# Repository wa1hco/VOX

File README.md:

# VOX — Voice Operated Switch for Ham Radio

A small-board VOX circuit using adaptive echo cancellation (AEC) and voice activity detection (VAD) to reliably key PTT from microphone audio while ignoring receive audio and background noise.

## Acronyms

- **AEC**: Adaptive Echo Cancellation
- **VAD**: Voice Activity Detection

## Features

- **AEC** — removes receive audio leaking into the microphone (anti-VOX), using SpeexDSP
- **VAD** — detects operator voice, ignores room noise, using SpeexDSP
- **Single control** — PTT hang time (ms); no level adjustments needed
- **3 LED status outputs**
	- `MIC LED`: microphone port activity/level present
	- `RX LED`: receive-audio port activity/level present
	- `VAD LED`: speech probability indicates likely operator voice
	- `AEC LED`: receive-audio leakage is being reduced by echo cancellation
	- `PTT LED`: transmit keying output is active
- **Linux simulation** — runs on a Linux PC for development and testing
- **MCU portable** — core library has no platform dependencies

## Building (Linux)

### Prerequisites

```sh
sudo apt install cmake libasound2-dev libspeexdsp-dev
```

For the Qt GUI on Linux:

```sh
sudo apt install qt6-base-dev
```

### Build

```sh
mkdir build && cd build
cmake ..
make
```

### Run

```sh
./vox_linux -h 500
```

Qt GUI run:

```sh
./vox_qt
```

The Qt test GUI shows:
- microphone level bargraph
- VAD output score (0-100)
- speaker monitor level bargraph
- AEC score (estimated reduction %)
- PTT ON/OFF indicator
- MCU-style LED panel: MIC, RX, VAD, AEC, PTT
- live tuning sliders for:
	- PTT hang time
	- MIC activity threshold
	- RX activity threshold
	- VAD probability threshold
	- AEC reduction threshold

By default on Linux desktop systems, `vox_linux` auto-selects:
- the default microphone source for `MIC`
- the monitor source of the default speaker sink for `RX`

Options:
- `--list-devices` — print available capture devices and exit
- `-m <device>` — microphone capture device (default `auto`)
- `-r <device>` — receive-reference capture device (default `auto`)
- `-h <ms>` — PTT hang time in milliseconds (default `500`)
- `-M <level>` — MIC LED activity threshold (default `300`)
- `-R <level>` — RX LED activity threshold (default `300`)
- `-V <pct>` — VAD LED probability threshold percent (default `60`)
- `-E <pct>` — AEC LED reduction threshold percent (default `20`)

Device string formats:
- ALSA: `hw:0,0`, `plughw:CARD=PCH,DEV=0`, `alsa:hw:0,0`
- Pulse source: `pulse:<source_name>`

To pick a specific mic + speaker-monitor pair on the current host, list the
devices first and copy two strings into `-m` / `-r`:

```sh
./vox_linux --list-devices
./vox_linux -m pulse:<your_mic_source> -r pulse:<your_sink>.monitor -h 500
```

The exact source names differ per machine — running across the desktop and
laptop is expected to give different `-m`/`-r` values.

The Linux runner prints LED transitions:
- `MIC` LED from raw mic level activity
- `RX` LED from receive reference level activity
- `PTT` LED from VOX state machine
- `VAD` LED from Speex VAD decision/probability
- `AEC` LED from measured mic-energy reduction while RX reference is active

## Tests

```sh
cd build
ctest --output-on-failure
```

Functional tests use synthetic audio. Regression tests load raw audio files from `tests/regression/data/` (see that directory for file format).

## Project Structure

```
src/                              Core library: vox.c, aec.c, vad.c
platform/linux/                   Linux ALSA/Pulse audio + Qt GUI
platform/mcu/
  core/                           Platform-independent MCU scaffold
    vox_mcu_board.h               Pin-config interface (VoxMcuPinConfig)
    vox_mcu_pins.h                GPIO port/pin uint8 encoding
    vox_mcu_decimator.{h,c}       32 MHz ADC → 8 kHz DSP CIC decimator
  boards/
    common/
      hco_pin_assignment.h        Shared HCO logical pin map
    stm32g474_vox_cb/             Custom STM32G474CBT3 board (LQFP48)
      board_pins.h                LQFP48 pin table + analog-front-end notes
      board.c                     Pin-config descriptor
      board.cmake                 Per-board CMake fragment
    stm32g474_nucleo/             NUCLEO-G474RE + HCO-mirrored shield
      board_pins.h                LQFP64 pin table + Nucleo-specific notes
      board.c
      board.cmake
cmake/
  arm-none-eabi.cmake             ARM cross-compile toolchain file
tests/                            Functional and regression tests (host)
docs/                             User manual and design description
```

## MCU builds (STM32G474)

The current MCU firmware is **bring-up only**: it blinks an LED, prints a
counter once a second on the debug UART, and proves the cross toolchain
+ linker script + flash workflow is alive.  ADC, OPAMP, DMA, USB, and
the actual VOX algorithm wiring land on top of this in later slices.

### Boards supported

- `stm32g474_nucleo` — NUCLEO-G474RE dev board with a prototype shield
  that mirrors the HCO custom-board pinout.  Bring-up uses the on-board
  ST-Link VCP (USART2 PA2/PA3 → `/dev/ttyACM0`).
- `stm32g474_vox_cb` — VOX HCO custom board (STM32G474CBT3, LQFP48).
  Bring-up uses USART1 PA9/PA10 with an external 3.3V USB-serial adapter.

Both boards share the same logical GPIO assignment via
`platform/mcu/boards/common/hco_pin_assignment.h`, so most MCU code is
identical between them.  Per-board files describe the package pinout
and any board-specific quirks (e.g. on the Nucleo, PA5 also drives the
on-board LD2 user LED, which is benign — it just mirrors `LED_MIC`).

Sample-rate plan (deferred until ADC driver lands):
- ADC front end runs at 32 kHz (4x oversampled vs the DSP rate)
- CIC decimation factor 4 → 8 kHz, gain R²=16 (no overflow concerns)
- AEC/VAD processing runs at 8 kHz

### One-time toolchain install (Ubuntu 24.04)

```sh
sudo apt-get update
sudo apt-get install -y \
    gcc-arm-none-eabi binutils-arm-none-eabi \
    libnewlib-arm-none-eabi libstdc++-arm-none-eabi-newlib \
    stlink-tools openocd \
    picocom
```

`gcc-arm-none-eabi` is the Cortex-M cross compiler; `stlink-tools`
provides `st-flash` / `st-info`; `openocd` is an alternative flasher
and SWD debug bridge; `picocom` is a tiny serial terminal for watching
UART output (`screen` or `minicom` work too).

After install, sanity-check:

```sh
arm-none-eabi-gcc --version       # expect 13.2.x
st-info --probe                   # expect to see a connected ST-Link if Nucleo plugged in
```

### Build, flash, and watch (Nucleo G474RE)

Plug the Nucleo into USB.  Linux should enumerate two devices:
- An ST-Link debug interface
- A USB Mass Storage drive labelled `NODE_G474RE` (for drag-drop flashing)
- A virtual COM port at `/dev/ttyACM0` (115200 8N1)

Then:

```sh
# Configure (cross-compile)
cmake -S . -B build-nucleo \
      -DCMAKE_TOOLCHAIN_FILE=cmake/arm-none-eabi.cmake \
      -DBOARD=stm32g474_nucleo

# Build the firmware (.elf + .bin + size report)
cmake --build build-nucleo

# Flash to the chip via the on-board ST-Link
cmake --build build-nucleo --target flash

# Open the VCP in another terminal to see "tick=N" lines and confirm life
picocom -b 115200 /dev/ttyACM0
#   ↑  Ctrl-A Ctrl-X to quit picocom
```

Expected output on `/dev/ttyACM0`:

```
VOX bringup: board=stm32g474_nucleo  sysclk=16MHz (HSI16)
LD2 (PA5) should be blinking at ~1 Hz.
tick=0
tick=1
tick=2
...
```

LD2 (the green LED next to the USER button) blinks at roughly 1 Hz.

### Build and flash (custom STM32G474CBT3 board)

```sh
cmake -S . -B build-vox-cb \
      -DCMAKE_TOOLCHAIN_FILE=cmake/arm-none-eabi.cmake \
      -DBOARD=stm32g474_vox_cb
cmake --build build-vox-cb
cmake --build build-vox-cb --target flash    # needs an external SWD probe
```

There is no on-board ST-Link, so connect an external probe (a Nucleo
used as ST-Link works) to the SWD pads, and an external 3.3V USB-serial
adapter to PA9/PA10 to see the `tick=N` output.

### Sanity-check the pin descriptor without a cross toolchain

If you want to verify the board descriptor + decimator compile but
haven't installed `arm-none-eabi-gcc` yet:

```sh
cmake -S . -B build-nucleo-host -DBOARD=stm32g474_nucleo
cmake --build build-nucleo-host --target vox_mcu_board
```

This builds `libvox_mcu_board.a` with the host gcc — the firmware
executable is intentionally skipped in this mode.

## Documentation

Design docs (in `docs/`):

- [user_stories.md](docs/user_stories.md) — the four user stories the
  app needs to serve (developer + operator faces)
- [dongle_protocol.md](docs/dongle_protocol.md) — wire protocol
  between vox_qt and the dongle firmware (frame format, message
  catalog, capability bits)
- [firmware_update.md](docs/firmware_update.md) — how dongle firmware
  updates work: USB DFU via the chip's ROM bootloader, soft-jumped
  from the running application via a `SET_MODE` command

Still to come:

- `user_manual.md` — installation and operation (placeholder)
- `design_description.md` — architecture and algorithm details (placeholder)

## License

TBD

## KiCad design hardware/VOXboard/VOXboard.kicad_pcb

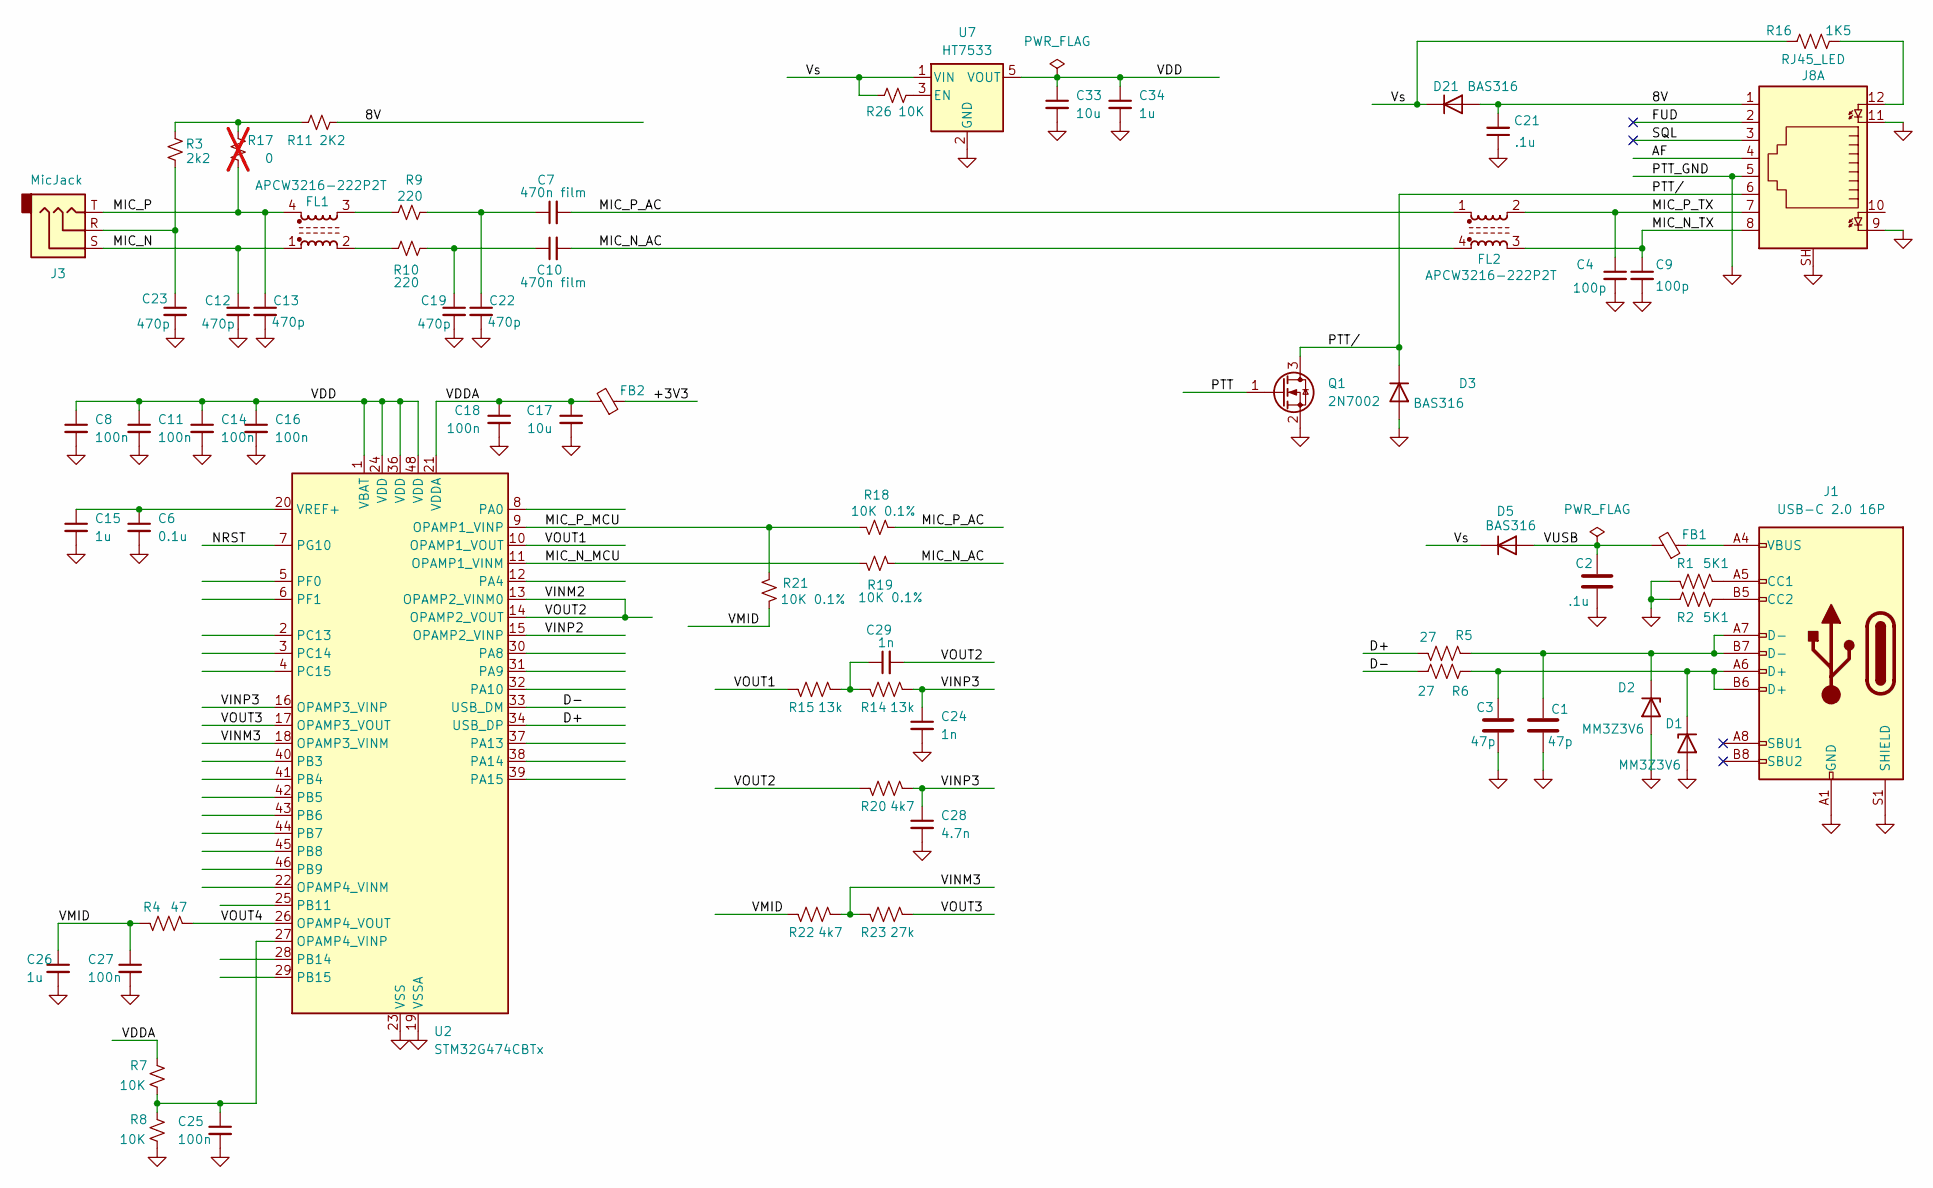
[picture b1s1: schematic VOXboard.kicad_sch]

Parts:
C1, C3: 47p; C_01005_0402Metric; LCSC C1671
C2: .1u; C_01005_0402Metric; LCSC C14663
C4, C9: 100p; C_01005_0402Metric
C6: 0.1u; C_01005_0402Metric
C7, C10: 470n film; C_01005_0402Metric
C8, C11, C14, C16, C18, C25, C27: 100n; C_01005_0402Metric
C12, C13, C19, C22, C23: 470p; C_01005_0402Metric
C15, C26, C34: 1u; C_01005_0402Metric
C17, C33: 10u; C_01005_0402Metric
C21: .1u; C_01005_0402Metric
C24, C29: 1n; C_01005_0402Metric
C28: 4.7n; C_01005_0402Metric
D1, D2: MM3Z3V6; D_SOD-323; LCSC C116949
D3, D5, D21: BAS316; D_SOD-323
FB1, FB2: FerriteBead_Small; L_0805_2012Metric; LCSC C1017
FL1, FL2: APCW3216-222P2T; L_CommonMode_Wurth_WE-CNSW-1206
J1: USB-C 2.0 16P; USB_C_Receptacle_G-Switch_GT-USB-7010ASV; LCSC C2988369
J3: MicJack; Jack_3.5mm_CUI_SJ1-3513N_Horizontal
J8: RJ45_LED; RJ45_Amphenol_RJHSE538X
Q1: 2N7002; SOT-23
R1, R2: 5K1; R_01005_0402Metric; LCSC C23186
R3: 2k2; R_01005_0402Metric
R4: 47; R_01005_0402Metric; LCSC PN C25190
R5, R6: 27; R_01005_0402Metric; LCSC PN C25190
R7, R8, R26: 10K; R_01005_0402Metric
R9, R10: 220; R_01005_0402Metric
R11: 2K2; R_01005_0402Metric
R14, R15: 13k; R_01005_0402Metric; LCSC PN C25190
R16: 1K5; R_01005_0402Metric; LCSC C21190
R17: 0; R_01005_0402Metric; not fitted
R18, R19, R21: 10K 0.1%; R_01005_0402Metric
R20, R22: 4k7; R_01005_0402Metric; LCSC PN C25190
R23: 27k; R_01005_0402Metric; LCSC PN C25190
U2: STM32G474CBTx; LQFP-48_7x7mm_P0.5mm
U7: HT7533; SOT-89-3

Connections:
/8V: C21.2, D21.2 (A), J8.1, R11.2
/+3V3: FB2.1
/AF: J8.4
/D+: R5.1, U2.34 (USB_DP)
/D-: R6.1, U2.33 (USB_DM)
/FUD: J8.2
/MIC_N: C12.1, FL1.1, J3.S
/MIC_N_AC: C10.2, FL2.4, R19.1
/MIC_N_MCU: R19.2, U2.11 (OPAMP1_VINM)
/MIC_N_TX: C9.1, FL2.3, J8.8
/MIC_P: C13.1, FL1.4, J3.T, R17.1
/MIC_P_AC: C7.2, FL2.1, R18.1
/MIC_P_MCU: R18.2, R21.2, U2.9 (OPAMP1_VINP)
/MIC_P_TX: C4.1, FL2.2, J8.7
/NRST: U2.7 (PG10)
/PTT: Q1.1 (G)
/PTT/: D3.1 (K), J8.6, Q1.3 (D)
/SQL: J8.3
/VDD: C8.1, C11.1, C14.1, C16.1, C33.1, C34.1, U2.1 (VBAT), U2.24 (VDD), U2.36 (VDD), U2.48 (VDD), U7.5 (VOUT)
/VDDA: C17.1, C18.1, FB2.2, R7.2, U2.21 (VDDA)
/VINM2: C29.2, R20.1, U2.13 (OPAMP2_VINM0), U2.14 (OPAMP2_VOUT)
/VINM3: R22.2, R23.1, U2.18 (OPAMP3_VINM)
/VINP2: U2.15 (OPAMP2_VINP)
/VINP3: C24.1, C28.1, R14.2, R20.2, U2.16 (OPAMP3_VINP)
/VMID: C26.1, C27.1, R4.1, R21.1, R22.1
/VOUT1: R15.1, U2.10 (OPAMP1_VOUT)
/VOUT3: R23.2, U2.17 (OPAMP3_VOUT)
/VOUT4: R4.2, U2.26 (OPAMP4_VOUT)
/VUSB: C2.1, D5.2 (A), FB1.2
/Vs: D5.1 (K), D21.1 (K), R16.1, R26.1, U7.1 (VIN)
GND: C1.2, C2.2, C3.2, C4.2, C6.2, C8.2, C9.2, C11.2, C12.2, C13.2, C14.2, C15.2, C16.2, C17.2, C18.2, C19.2, C21.1, C22.2, C23.2, C24.2, C25.2, C26.2, C27.2, C28.2, C33.2, C34.2, D1.2 (A), D2.2 (A), D3.2 (A), J1.A1 (GND), J1.A12 (GND), J1.B1 (GND), J1.B12 (GND), J1.S1 (SHIELD), J8.5, J8.9, J8.11, J8.SH, Q1.2 (S), R1.1, R2.1, R8.1, U2.19 (VSSA), U2.23 (VSS), U2.35 (VSS), U2.47 (VSS), U7.2 (GND)
unnamed: C10.1, C19.1, R10.2
unnamed: C7.1, C22.1, R9.2
unnamed: C23.1, J3.R, R3.1
unnamed: C29.1, R14.1, R15.2
unnamed: C3.1, D1.1 (K), J1.A6 (D+), J1.B6 (D+), R6.2
unnamed: C1.1, D2.1 (K), J1.A7 (D-), J1.B7 (D-), R5.2
unnamed: FB1.1, J1.A4 (VBUS), J1.A9 (VBUS), J1.B4 (VBUS), J1.B9 (VBUS)
unnamed: FL1.2, R10.1
unnamed: FL1.3, R9.1
unnamed: J1.A5 (CC1), R1.2
unnamed: J1.B5 (CC2), R2.2
unnamed: J8.12, R16.2
unnamed: R3.2, R11.1, R17.2
unnamed: C25.1, R7.1, R8.2, U2.27 (OPAMP4_VINP)
unnamed: C6.1, C15.1, U2.20 (VREF+)
unnamed: R26.2, U7.3 (EN)

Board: 2 copper layers, 66 parts (0 on the bottom side), 40 nets, no tracks yet.

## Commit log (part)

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2026-05-01 VOX algorithm runs on a linux laptop using Voice Activity Detection and Automatic Echo Cancellation. Hardware design is just starting
2026-05-02 mcu: migrate scaffold to stm32g474 and add 32MHz->8kHz adc decimator
2026-05-11 Worked on OpAmp design in uSimmics. Updated schematic.
